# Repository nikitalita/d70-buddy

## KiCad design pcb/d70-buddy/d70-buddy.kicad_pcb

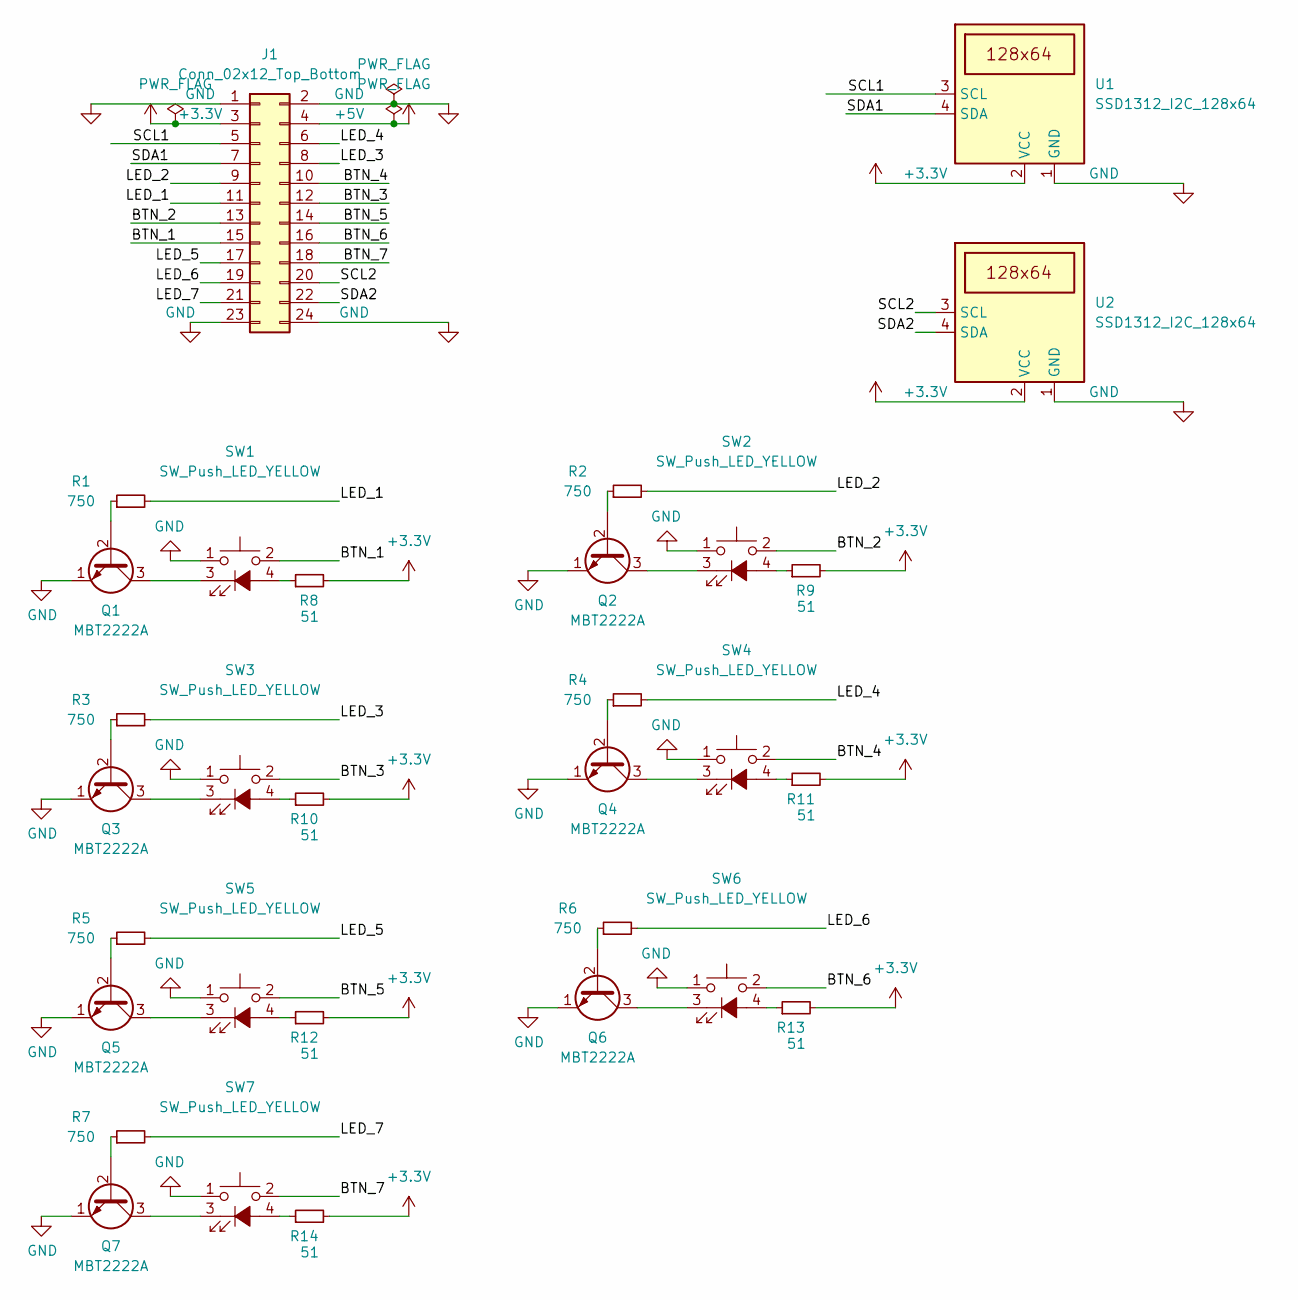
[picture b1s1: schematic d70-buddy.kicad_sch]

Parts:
J1: Conn_02x12_Top_Bottom; PinHeader_2x12_P2.54mm_Vertical
Q1, Q2, Q3, Q4, Q5, Q6, Q7: MBT2222A
R1, R2, R3, R4, R5, R6, R7: 750; R_0805_2012Metric_Pad1.20x1.40mm_HandSolder
R8, R9, R10, R11, R12, R13, R14: 51; R_0805_2012Metric_Pad1.20x1.40mm_HandSolder
SW1, SW2, SW3, SW4, SW5, SW6, SW7: SW_Push_LED_YELLOW; SW_PUSH_LED_6mm_H7.3mm
U1, U2: SSD1312_I2C_128x64; OLED_SSD1312_I2C_0.96_No_Mounting_Holes

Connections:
+3V3: J1.3, R8.2, R9.2, R10.2, R11.2, R12.2, R13.2, R14.2, U1.2 (VCC), U2.2 (VCC)
+5V: J1.4
/BTN_1: J1.15, SW1.2
/BTN_2: J1.13, SW2.2
/BTN_3: J1.12, SW3.2
/BTN_4: J1.10, SW4.2
/BTN_5: J1.14, SW5.2
/BTN_6: J1.16, SW6.2
/BTN_7: J1.18, SW7.2
/LED_1: J1.11, R1.2
/LED_2: J1.9, R2.2
/LED_3: J1.8, R3.2
/LED_4: J1.6, R4.2
/LED_5: J1.17, R5.2
/LED_6: J1.19, R6.2
/LED_7: J1.21, R7.2
/SCL1: J1.5, U1.3 (SCL)
/SCL2: J1.20, U2.3 (SCL)
/SDA1: J1.7, U1.4 (SDA)
/SDA2: J1.22, U2.4 (SDA)
GND: J1.1, J1.2, J1.23, J1.24, Q1.1 (E), Q2.1 (E), Q3.1 (E), Q4.1 (E), Q5.1 (E), Q6.1 (E), Q7.1 (E), SW1.1, SW2.1, SW3.1, SW4.1, SW5.1, SW6.1, SW7.1, U1.1 (GND), U2.1 (GND)
unnamed: Q1.2 (B), R1.1
unnamed: Q1.3 (C), SW1.3 (K)
unnamed: Q2.2 (B), R2.1
unnamed: Q2.3 (C), SW2.3 (K)
unnamed: Q3.2 (B), R3.1
unnamed: Q3.3 (C), SW3.3 (K)
unnamed: Q4.2 (B), R4.1
unnamed: Q4.3 (C), SW4.3 (K)
unnamed: Q5.2 (B), R5.1
unnamed: Q5.3 (C), SW5.3 (K)
unnamed: Q6.2 (B), R6.1
unnamed: Q6.3 (C), SW6.3 (K)
unnamed: Q7.2 (B), R7.1
unnamed: Q7.3 (C), SW7.3 (K)
unnamed: R8.1, SW1.4 (A)
unnamed: R9.1, SW2.4 (A)
unnamed: R10.1, SW3.4 (A)
unnamed: R11.1, SW4.4 (A)
unnamed: R12.1, SW5.4 (A)
unnamed: R13.1, SW6.4 (A)
unnamed: R14.1, SW7.4 (A)

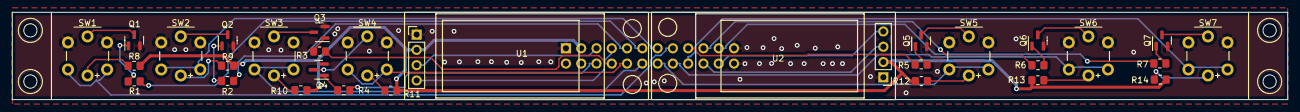
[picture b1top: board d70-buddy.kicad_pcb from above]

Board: 2 copper layers, 212.0 x 14.5 mm, 35 parts (1 on the bottom side), 41 nets.

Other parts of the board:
H1, H2, H3, H4: MountingHole_2.2mm_M2

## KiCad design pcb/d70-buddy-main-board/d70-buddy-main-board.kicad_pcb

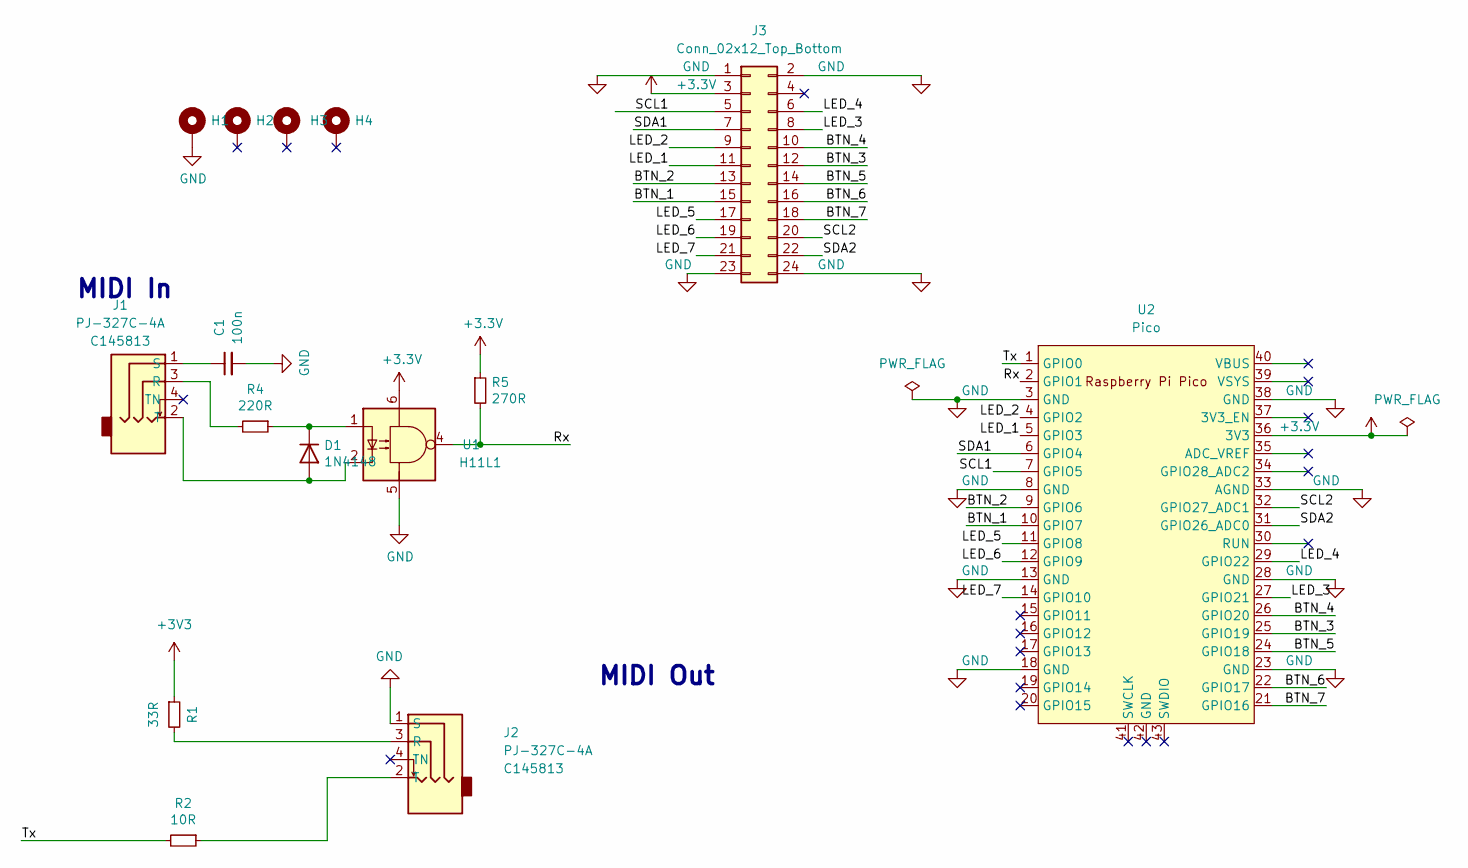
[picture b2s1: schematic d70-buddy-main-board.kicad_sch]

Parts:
C1: 100n; C_0805_2012Metric
D1: 1N4148; D_SOD-123
H1, H2, H3, H4: MountingHole_3.2mm_M3_ISO7380_Pad
J1, J2: PJ-327C-4A; LCSC Part # C145813
J3: Conn_02x12_Top_Bottom; PinHeader_2x12_P2.54mm_Vertical
R1: 33R; R_0805_2012Metric; Mouser 667-ERJ-6ENF2200V
R2: 10R; R_0805_2012Metric; Mouser 667-ERJ-6ENF2200V
R4: 220R; R_0805_2012Metric; Mouser 667-ERJ-6ENF2200V
R5: 270R; R_0805_2012Metric; Mouser 667-ERJ-6ENF1002V
U1: H11L1; Everlight_H11L1S
U2: Pico; RPi_Pico_SMD_TH

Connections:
/BTN_1: J3.15, U2.10 (GPIO7)
/BTN_2: J3.13, U2.9 (GPIO6)
/BTN_3: J3.12, U2.25 (GPIO19)
/BTN_4: J3.10, U2.26 (GPIO20)
/BTN_5: J3.14, U2.24 (GPIO18)
/BTN_6: J3.16, U2.22 (GPIO17)
/BTN_7: J3.18, U2.21 (GPIO16)
/LED_1: J3.11, U2.5 (GPIO3)
/LED_2: J3.9, U2.4 (GPIO2)
/LED_3: J3.8, U2.27 (GPIO21)
/LED_4: J3.6, U2.29 (GPIO22)
/LED_5: J3.17, U2.11 (GPIO8)
/LED_6: J3.19, U2.12 (GPIO9)
/LED_7: J3.21, U2.14 (GPIO10)
/Rx: R5.2, U1.4, U2.2 (GPIO1)
/SCL1: J3.5, U2.7 (GPIO5)
/SCL2: J3.20, U2.32 (GPIO27_ADC1)
/SDA1: J3.7, U2.6 (GPIO4)
/SDA2: J3.22, U2.31 (GPIO26_ADC0)
/Tx: R2.2, U2.1 (GPIO0)
GND: C1.2, H1.1, J2.1 (S), J3.1, J3.2, J3.23, J3.24, U1.5, U2.3 (GND), U2.8 (GND), U2.13 (GND), U2.18 (GND), U2.23 (GND), U2.28 (GND), U2.33 (AGND), U2.38 (GND)
unnamed: D1.1 (K), R4.1, U1.1
unnamed: D1.2 (A), J1.2 (T), U1.2
unnamed: C1.1, J1.1 (S)
unnamed: J2.3 (R), R1.2
unnamed: J2.2 (T), R2.1
unnamed: J1.3 (R), R4.2

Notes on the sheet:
MIDI In
MIDI Out

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
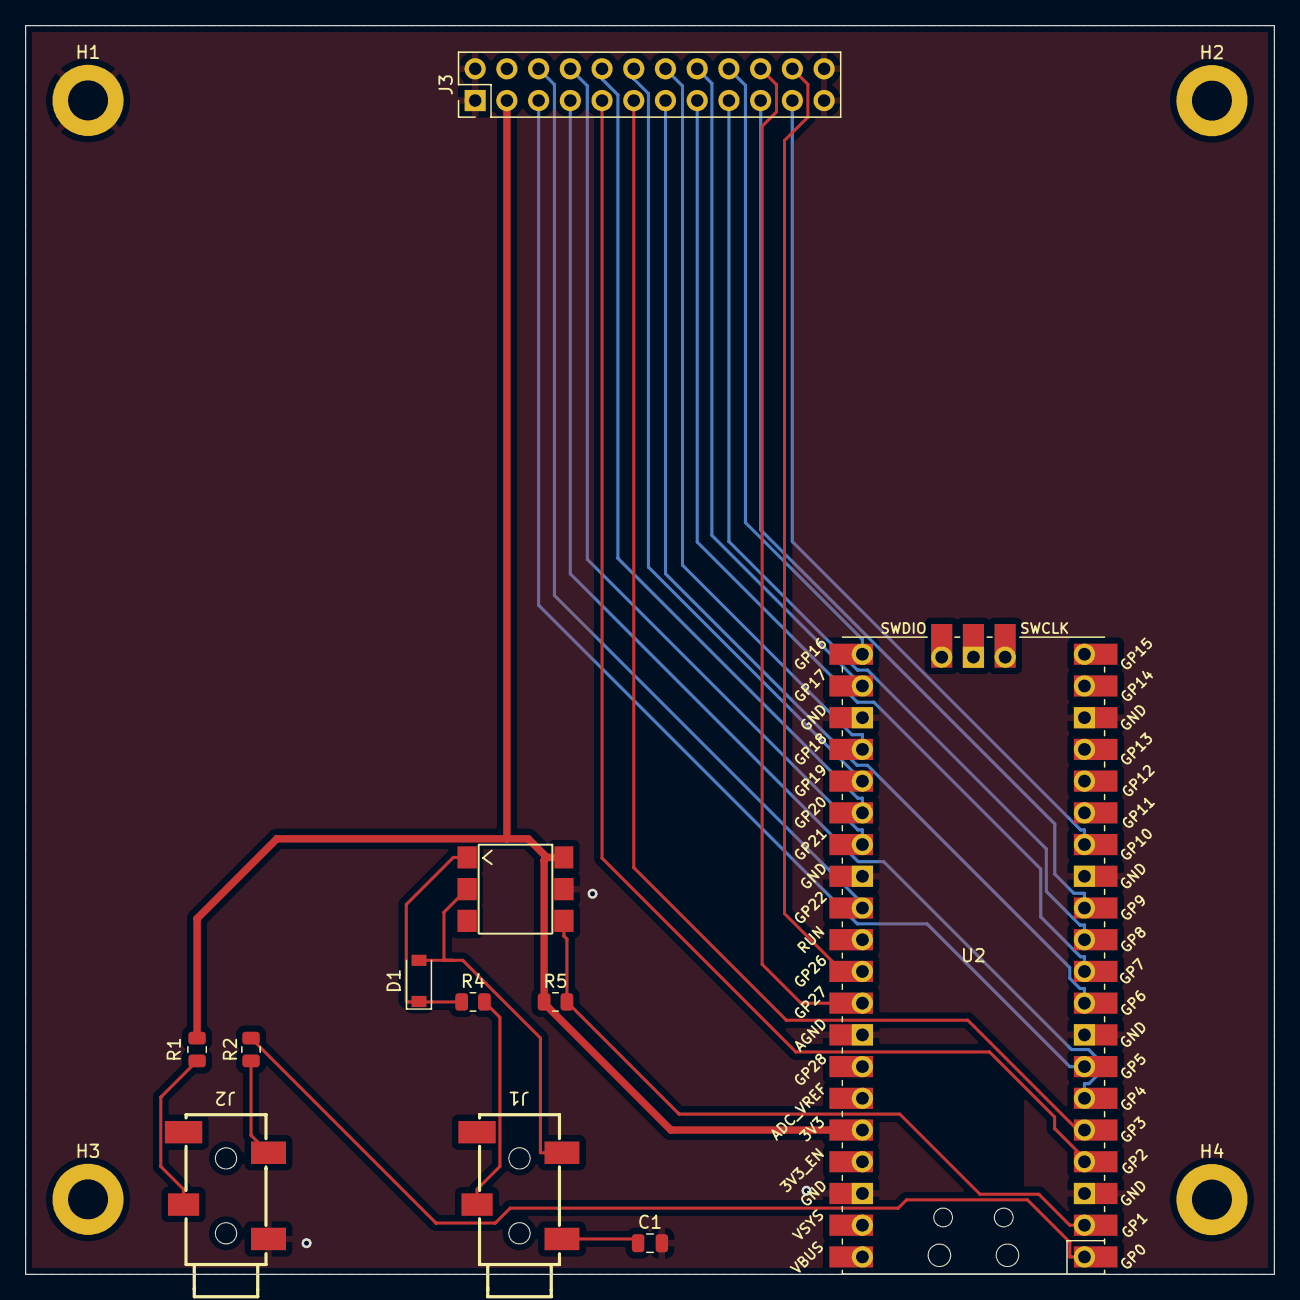
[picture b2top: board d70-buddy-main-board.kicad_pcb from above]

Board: 2 copper layers, 100.0 x 100.0 mm, 15 parts (0 on the bottom side), 28 nets.

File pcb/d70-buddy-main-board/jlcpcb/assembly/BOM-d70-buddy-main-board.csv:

Comment,Designator,Footprint,LCSC
PJ-327C-4A,"J1,J2",PJ-327C-4A,C145813
10R,R2,R_0805_2012Metric,C17415
220R,R4,R_0805_2012Metric,C17557
270R,R5,R_0805_2012Metric,C17590
33R,R1,R_0805_2012Metric,C17634
100n,C1,C_0805_2012Metric,C28233
H11L1,U1,Everlight_H11L1S,C78589
1N4148,D1,D_SOD-123,C81598
MountingHole_3.2mm_M3_ISO7380_Pad,H1,MountingHole_3.2mm_M3_ISO7380_Pad,
MountingHole_3.2mm_M3_ISO7380_Pad,H2,MountingHole_3.2mm_M3_ISO7380_Pad,
MountingHole_3.2mm_M3_ISO7380_Pad,H4,MountingHole_3.2mm_M3_ISO7380_Pad,
MountingHole_3.2mm_M3_ISO7380_Pad,H3,MountingHole_3.2mm_M3_ISO7380_Pad,
Conn_02x12_Top_Bottom,J3,PinHeader_2x12_P2.54mm_Vertical,
Pico,U2,RPi_Pico_SMD_TH,

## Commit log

2022-03-15 more pcb stuff
